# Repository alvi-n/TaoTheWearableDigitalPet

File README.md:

# Tao - A Palm-Sized, Sensor-Driven Dynamic Digital Pet ⭐

Tao is a highly responsive, accessible companion device that uses an **accelerometer** much like on phones that detect orientation to switch from portrait to landscape mode. It also utilizes a **temperature sensor** and **haptic motors** that vibrate, which all triggers unique face animations.

Over the past few months, I've been seeing this unique hardware accessory called ["Starboy" by CREATURE](https://hesjustalittleguy.com/). It features a palm-sized digital pet that has a star-shaped form factor and a round screen in the middle with very expressive eyes. As you can probably tell by the title description, this project was heavily inspired by this. I was immediately captivated by the concept, but with the original product selling for around $150 to $300, I thought it felt like a great open-source, diy project.
> _"STARBOY perceives its environment through a camera, microphone, temperature sensor, and accelerometer. bring him into a loud environment and he gets anxious. Leave him in the cold and he shivers. Shake him and he gets dizzy and mad at you. give him a thumbs up to check the battery level, or flick him off if you feel like making him sad."_

## Hardware
- Seeed XIAO ESP32-S3
- Round GC9A01 SPI LCD
- LSM6DSL accelerometer (I2C)
- PCT2075D Temperature sensor (I2C)
- DRV2605L haptic driver (I2C, shared bus)
- 3.7V 300mAh LiPo battery

| Schematic | PCB | Render |
| ----- | ---- | ---- |
|  |  | 

## What It Does
- Two animated eyes are Tao's entire face
- An LSM6DSL accelerometer notes any change in motion in real time
  -The accelerometer reads the change in acceleration magnitude between frames and sorts it into still / moving / shake states
  - This is very similar to how your phone can detect if your screen is turned so you could watch videos fullscreen
- A haptic motor creates different unique haptic patterns depending on what Tao is going through
- Uses an ESP32-S3 development board to make power management easier

## Future Plans
- Add additional states for more interactions
- Use a deburring tool to round out all the edges
### If done again...
- NFC Chip - Originally this was supposed to have one but making a custom antenna was a diffcult process in such a limited space
- No modules - this means all power managment will have to be designed from scratch and same with the screen module
- Add more inputs like a microphone, camera, photoresistor, etc

BOM
| item | quantity | Link | Price |
| --- | --- | --- | --- |
| LSM6DSVQTR | 1 | lcsc | $12.04 |
| DRV2605LYZFR | 1 | lcsc | $6.75 |
| 10kΩ Resistor | 2 | lcsc | $0.03 |
| 100nF Capacitors | 4 | lscs | $0.34 |
| Seeed XIAO ESP32-S3 | 1 | https://www.seeedstudio.com/XIAO-ESP32S3-p-5627.html | $7.49 |
| 3.7V 300mAh 502035 LiPo | 1 | https://a.co/d/0aBGCeCJ | $9 |
| Round LCD Module GC9A01 | 1 | https://tinyurl.com/yj44nenv | $2 |
| LRA Haptic Motor| 1 | https://www.adafruit.com/product/1201 | $6 |
| PCT2075D Temperature Sensor| 1 | lcsc | $2.07 |
| Plastic Case | 3D - Printed |

> [!NOTE]
> Estimated Total Price: ~$75 USD with shipping 
> JLC PCBA charges an extra $21.77 for fees

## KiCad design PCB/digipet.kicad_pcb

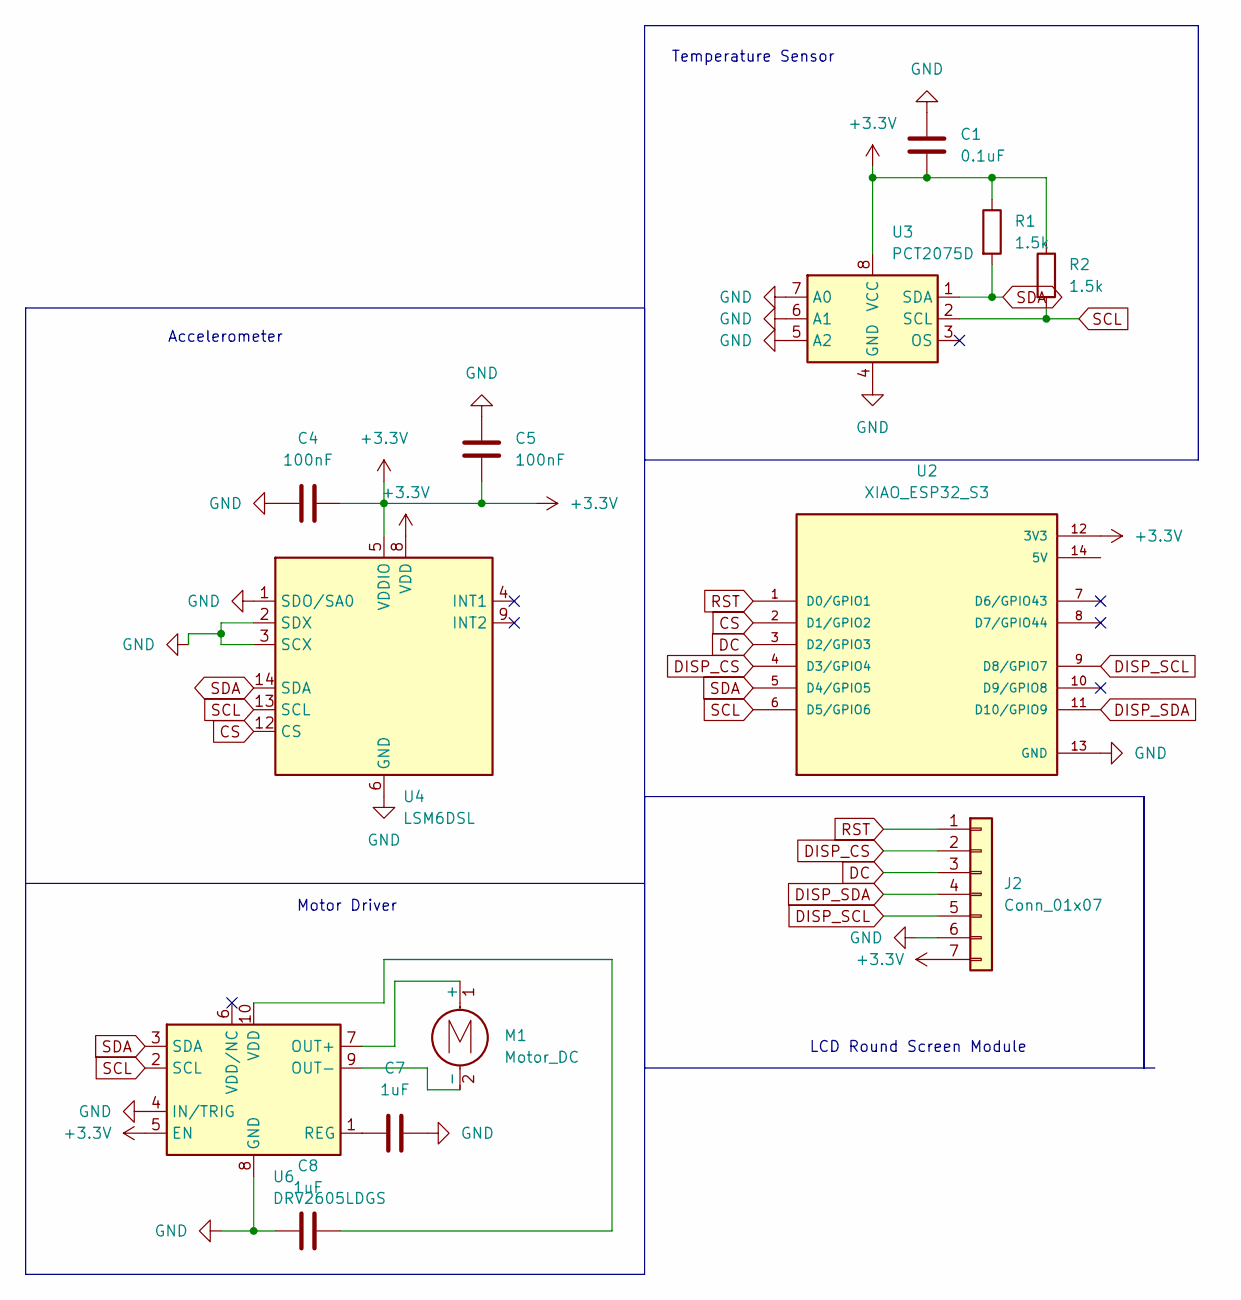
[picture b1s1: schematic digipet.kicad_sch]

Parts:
C1: 0.1uF; C_0805_2012Metric
C4, C5: 100nF; C_0805_2012Metric
C7, C8: 1uF; C_0805_2012Metric
J2: Conn_01x07; PinHeader_1x07_P2.54mm_Vertical
M1: Motor_DC; SolderWire-0.5sqmm_1x02_P4.6mm_D0.9mm_OD2.1mm
R1, R2: 1.5k; R_0805_2012Metric
U2: XIAO_ESP32_S3; MODULE_XIAO_ESP32_S3; PARTREV April 22nd, 2026
U3: PCT2075D; SO-8_3.9x4.9mm_P1.27mm
U4: LSM6DSL; LGA-14_3x2.5mm_P0.5mm_LayoutBorder3x4y
U6: DRV2605LDGS; VSSOP-10_3x3mm_P0.5mm

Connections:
+3.3V: C1.2, C4.2, C5.2, J2.7, R1.1, R2.1, U2.12 (3V3), U3.8 (VCC), U4.5 (VDDIO), U4.8 (VDD), U6.5 (EN)
CS: U2.2 (D1/GPIO2), U4.12 (CS)
DC: J2.3, U2.3 (D2/GPIO3)
DISP_CS: J2.2, U2.4 (D3/GPIO4)
DISP_SCL: J2.5, U2.9 (D8/GPIO7)
DISP_SDA: J2.4, U2.11 (D10/GPIO9)
GND: C1.1, C4.1, C5.1, C7.2, C8.1, J2.6, U2.13 (GND), U3.4 (GND), U3.5 (A2), U3.6 (A1), U3.7 (A0), U4.1 (SDO/SA0), U4.2 (SDX), U4.3 (SCX), U4.6 (GND), U4.7 (GND), U6.4 (IN/TRIG), U6.8 (GND)
unnamed: M1.1 (+), U6.7 (OUT+)
unnamed: M1.2 (-), U6.9 (OUT-)
unnamed: C7.1, U6.1 (REG)
unnamed: C8.2, U6.10 (VDD)
RST: J2.1, U2.1 (D0/GPIO1)
SCL: R2.2, U2.6 (D5/GPIO6), U3.2 (SCL), U4.13 (SCL), U6.2 (SCL)
SDA: R1.2, U2.5 (D4/GPIO5), U3.1 (SDA), U4.14 (SDA), U6.3 (SDA)

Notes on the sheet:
Motor Driver
Temperature Sensor
Accelerometer
LCD Round Screen Module

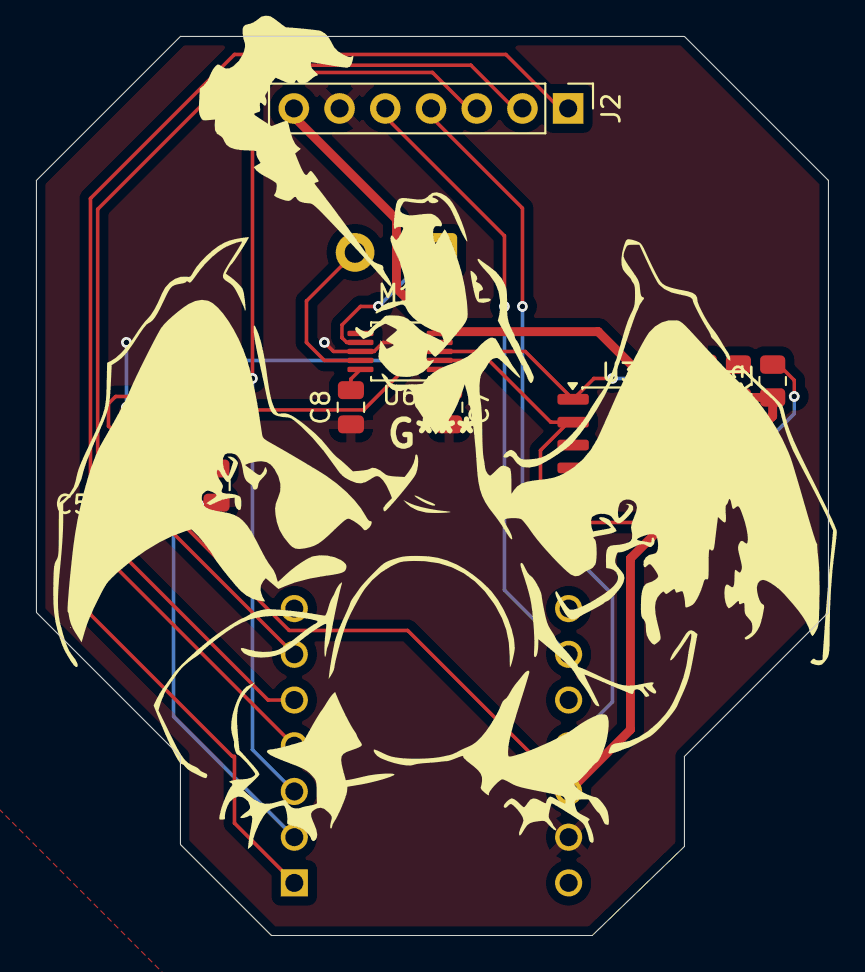
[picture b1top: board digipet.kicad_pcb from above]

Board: 2 copper layers, 44.0 x 49.9 mm, 13 parts (1 on the bottom side), 14 nets.
